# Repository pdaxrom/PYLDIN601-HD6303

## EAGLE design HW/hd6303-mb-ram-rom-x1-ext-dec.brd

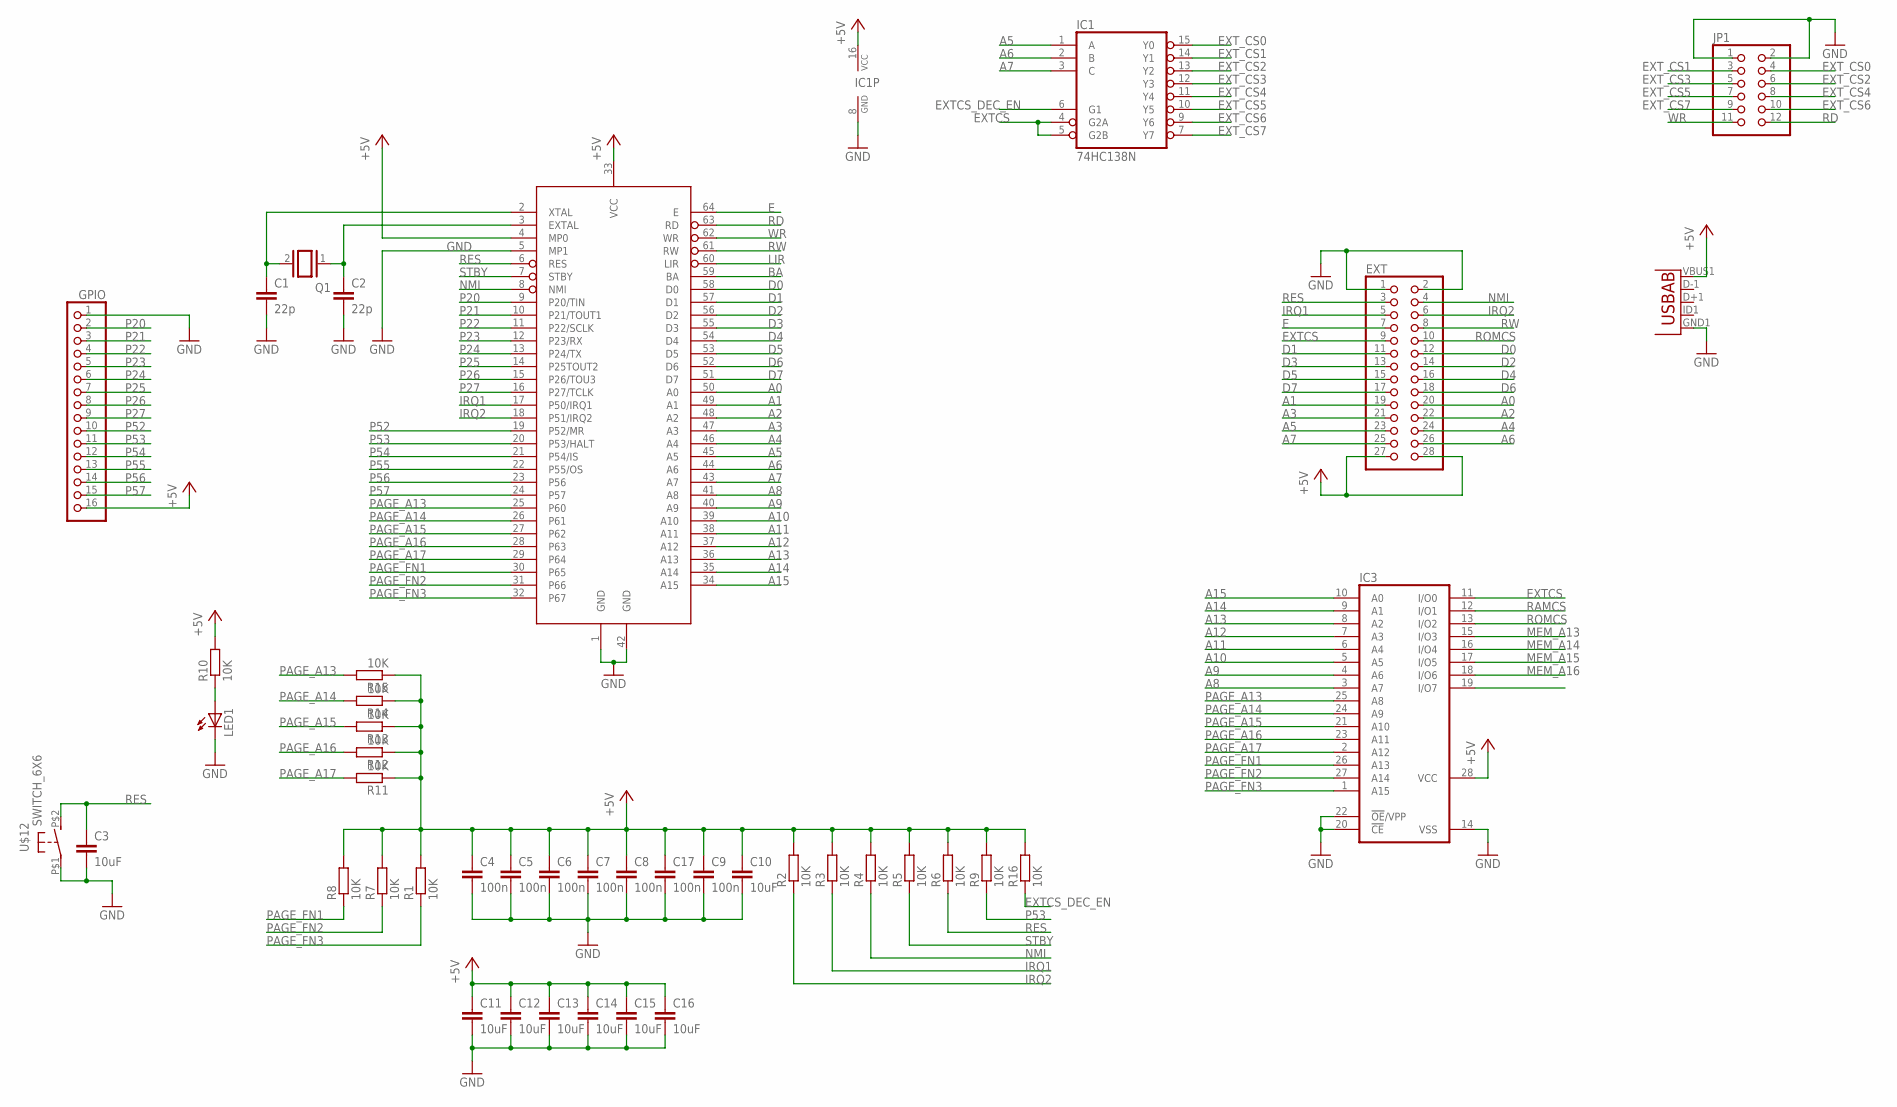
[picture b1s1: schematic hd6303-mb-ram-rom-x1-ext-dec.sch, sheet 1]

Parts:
C1, C2: 22p; C0603
C3, C10, C11, C12, C13, C14, C15, C16: 10uF; C0805
C4, C5, C6, C7, C8, C9, C17: 100n; C0603
EXT: PINHD-2X14; 2X14
GPIO: PINHD-1X16; 1X16
IC1: 74HC138N; DIL16
IC3: 27512G; DIL28-6
JP1: PINHD-2X6; 2X06
LED1: LED5MM
Q1: XTAL/S; QS
R1, R2, R3, R4, R5, R6, R7, R8, R9, R10, R11, R12, R13, R14, R15, R16: 10K; R0603
U2: USB""; USB-MICRO-SMD
U$1: HD6303YCP; DP-64S
U$12: SWITCH_6X6

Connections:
+5V: C4.1, C5.1, C6.1, C7.1, C8.1, C9.1, C10.1, C11.1, C12.1, C13.1, C14.1, C15.1, C16.1, C17.1, EXT.27, EXT.28, GPIO.16, IC1.16 (VCC), IC3.28 (VCC), R1.2, R2.2, R3.2, R4.2, R5.2, R6.2, R7.2, R8.2, R9.2, R10.2, R11.1, R12.1, R13.1, R14.1, R15.1, R16.2, U2.VBUS1 (VBUS), U$1.4 (MP0), U$1.33 (VCC); also elsewhere on the board
A0: EXT.20, U$1.50 (A0); also elsewhere on the board
A1: EXT.19, U$1.49 (A1); also elsewhere on the board
A2: EXT.22, U$1.48 (A2); also elsewhere on the board
A3: EXT.21, U$1.47 (A3); also elsewhere on the board
A4: EXT.24, U$1.46 (A4); also elsewhere on the board
A5: EXT.23, IC1.1 (A), U$1.45 (A5); also elsewhere on the board
A6: EXT.26, IC1.2 (B), U$1.44 (A6); also elsewhere on the board
A7: EXT.25, IC1.3 (C), U$1.43 (A7); also elsewhere on the board
A8: IC3.3 (A7), U$1.41 (A8); also elsewhere on the board
A9: IC3.4 (A6), U$1.40 (A9); also elsewhere on the board
A10: IC3.5 (A5), U$1.39 (A10); also elsewhere on the board
A11: IC3.6 (A4), U$1.38 (A11); also elsewhere on the board
A12: IC3.7 (A3), U$1.37 (A12); also elsewhere on the board
A13: IC3.8 (A2), U$1.36 (A13)
A14: IC3.9 (A1), U$1.35 (A14)
A15: IC3.10 (A0), U$1.34 (A15)
BA: U$1.59 (BA)
D0: EXT.12, U$1.58 (D0); also elsewhere on the board
D1: EXT.11, U$1.57 (D1); also elsewhere on the board
D2: EXT.14, U$1.56 (D2); also elsewhere on the board
D3: EXT.13, U$1.55 (D3); also elsewhere on the board
D4: EXT.16, U$1.54 (D4); also elsewhere on the board
D5: EXT.15, U$1.53 (D5); also elsewhere on the board
D6: EXT.18, U$1.52 (D6); also elsewhere on the board
D7: EXT.17, U$1.51 (D7); also elsewhere on the board
E: EXT.7, U$1.64 (E)
EXTCS: EXT.9, IC1.4 (G2A), IC1.5 (G2B), IC3.11 (I/O0)
EXTCS_DEC_EN: IC1.6 (G1), R16.1
EXT_CS0: IC1.15 (Y0), JP1.4
EXT_CS1: IC1.14 (Y1), JP1.3
EXT_CS2: IC1.13 (Y2), JP1.6
EXT_CS3: IC1.12 (Y3), JP1.5
EXT_CS4: IC1.11 (Y4), JP1.8
EXT_CS5: IC1.10 (Y5), JP1.7
EXT_CS6: IC1.9 (Y6), JP1.10
EXT_CS7: IC1.7 (Y7), JP1.9
GND: C1.2, C2.2, C3.2, C4.2, C5.2, C6.2, C7.2, C8.2, C9.2, C10.2, C11.2, C12.2, C13.2, C14.2, C15.2, C16.2, C17.2, EXT.1, EXT.2, GPIO.1, IC1.8 (GND), IC3.14 (VSS), IC3.20 (!CE), IC3.22 (!OE!/VPP), JP1.1, JP1.2, LED1.K (C), U2.GND1 (GND), U$1.1 (GND), U$1.5 (MP1), U$1.42 (GND), U$12.P$1; also elsewhere on the board
IRQ1: EXT.5, R3.1, U$1.17 (P50/IRQ1)
IRQ2: EXT.6, R2.1, U$1.18 (P51/IRQ2)
LIR: U$1.60 (LIR)
MEM_A13: IC3.15 (I/O3); also elsewhere on the board
MEM_A14: IC3.16 (I/O4); also elsewhere on the board
MEM_A15: IC3.17 (I/O5); also elsewhere on the board
MEM_A16: IC3.18 (I/O6); also elsewhere on the board
unnamed: LED1.A, R10.1
unnamed: C1.1, Q1.2, U$1.2 (XTAL)
unnamed: C2.1, Q1.1, U$1.3 (EXTAL)
NMI: EXT.4, R4.1, U$1.8 (NMI)
P20: GPIO.2, U$1.9 (P20/TIN)
P21: GPIO.3, U$1.10 (P21/TOUT1)
P22: GPIO.4, U$1.11 (P22/SCLK)
P23: GPIO.5, U$1.12 (P23/RX)
P24: GPIO.6, U$1.13 (P24/TX)
P25: GPIO.7, U$1.14 (P25TOUT2)
P26: GPIO.8, U$1.15 (P26/TOU3)
P27: GPIO.9, U$1.16 (P27/TCLK)
P52: GPIO.10, U$1.19 (P52/MR)
P53: GPIO.11, R9.1, U$1.20 (P53/HALT)
P54: GPIO.12, U$1.21 (P54/IS)
P55: GPIO.13, U$1.22 (P55/OS)
P56: GPIO.14, U$1.23 (P56)
P57: GPIO.15, U$1.24 (P57)
PAGE_A13: IC3.25 (A8), R15.2, U$1.25 (P60)
PAGE_A14: IC3.24 (A9), R14.2, U$1.26 (P61)
PAGE_A15: IC3.21 (A10), R13.2, U$1.27 (P62)
PAGE_A16: IC3.23 (A11), R12.2, U$1.28 (P63)
PAGE_A17: IC3.2 (A12), R11.2, U$1.29 (P64)
PAGE_FN1: IC3.26 (A13), R8.1, U$1.30 (P65)
PAGE_FN2: IC3.27 (A14), R7.1, U$1.31 (P66)
PAGE_FN3: IC3.1 (A15), R1.1, U$1.32 (P67)
RAMCS: IC3.12 (I/O1); also elsewhere on the board
RD: JP1.12, U$1.63 (RD); also elsewhere on the board
RES: C3.1, EXT.3, R6.1, U$1.6 (RES), U$12.P$2 (S)
ROMCS: EXT.10, IC3.13 (I/O2); also elsewhere on the board
RW: EXT.8, U$1.61 (RW)
STBY: R5.1, U$1.7 (STBY)
WR: JP1.11, U$1.62 (WR); also elsewhere on the board

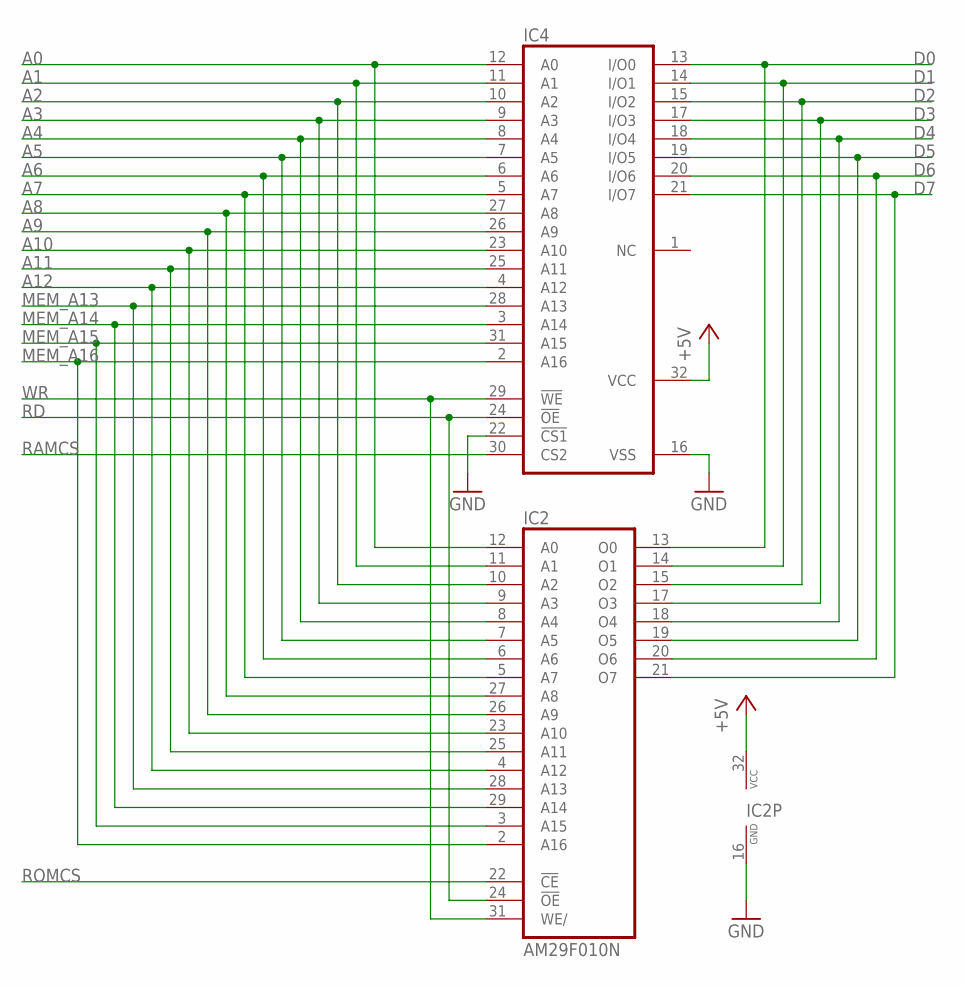
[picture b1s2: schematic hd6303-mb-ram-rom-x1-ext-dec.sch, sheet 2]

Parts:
IC2: AM29F010N; DIP32
IC4: 628128P; DIL32

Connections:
+5V: IC2.32 (VCC), IC4.32 (VCC); also elsewhere on the board
A0: IC2.12 (A0), IC4.12 (A0); also elsewhere on the board
A1: IC2.11 (A1), IC4.11 (A1); also elsewhere on the board
A2: IC2.10 (A2), IC4.10 (A2); also elsewhere on the board
A3: IC2.9 (A3), IC4.9 (A3); also elsewhere on the board
A4: IC2.8 (A4), IC4.8 (A4); also elsewhere on the board
A5: IC2.7 (A5), IC4.7 (A5); also elsewhere on the board
A6: IC2.6 (A6), IC4.6 (A6); also elsewhere on the board
A7: IC2.5 (A7), IC4.5 (A7); also elsewhere on the board
A8: IC2.27 (A8), IC4.27 (A8); also elsewhere on the board
A9: IC2.26 (A9), IC4.26 (A9); also elsewhere on the board
A10: IC2.23 (A10), IC4.23 (A10); also elsewhere on the board
A11: IC2.25 (A11), IC4.25 (A11); also elsewhere on the board
A12: IC2.4 (A12), IC4.4 (A12); also elsewhere on the board
D0: IC2.13 (O0), IC4.13 (I/O0); also elsewhere on the board
D1: IC2.14 (O1), IC4.14 (I/O1); also elsewhere on the board
D2: IC2.15 (O2), IC4.15 (I/O2); also elsewhere on the board
D3: IC2.17 (O3), IC4.17 (I/O3); also elsewhere on the board
D4: IC2.18 (O4), IC4.18 (I/O4); also elsewhere on the board
D5: IC2.19 (O5), IC4.19 (I/O5); also elsewhere on the board
D6: IC2.20 (O6), IC4.20 (I/O6); also elsewhere on the board
D7: IC2.21 (O7), IC4.21 (I/O7); also elsewhere on the board
GND: IC2.16 (GND), IC4.16 (VSS), IC4.22 (!CS1); also elsewhere on the board
MEM_A13: IC2.28 (A13), IC4.28 (A13); also elsewhere on the board
MEM_A14: IC2.29 (A14), IC4.3 (A14); also elsewhere on the board
MEM_A15: IC2.3 (A15), IC4.31 (A15); also elsewhere on the board
MEM_A16: IC2.2 (A16), IC4.2 (A16); also elsewhere on the board
RAMCS: IC4.30 (CS2); also elsewhere on the board
RD: IC2.24 (!OE), IC4.24 (!OE); also elsewhere on the board
ROMCS: IC2.22 (!CE); also elsewhere on the board
WR: IC2.31 (WE/), IC4.29 (!WE); also elsewhere on the board

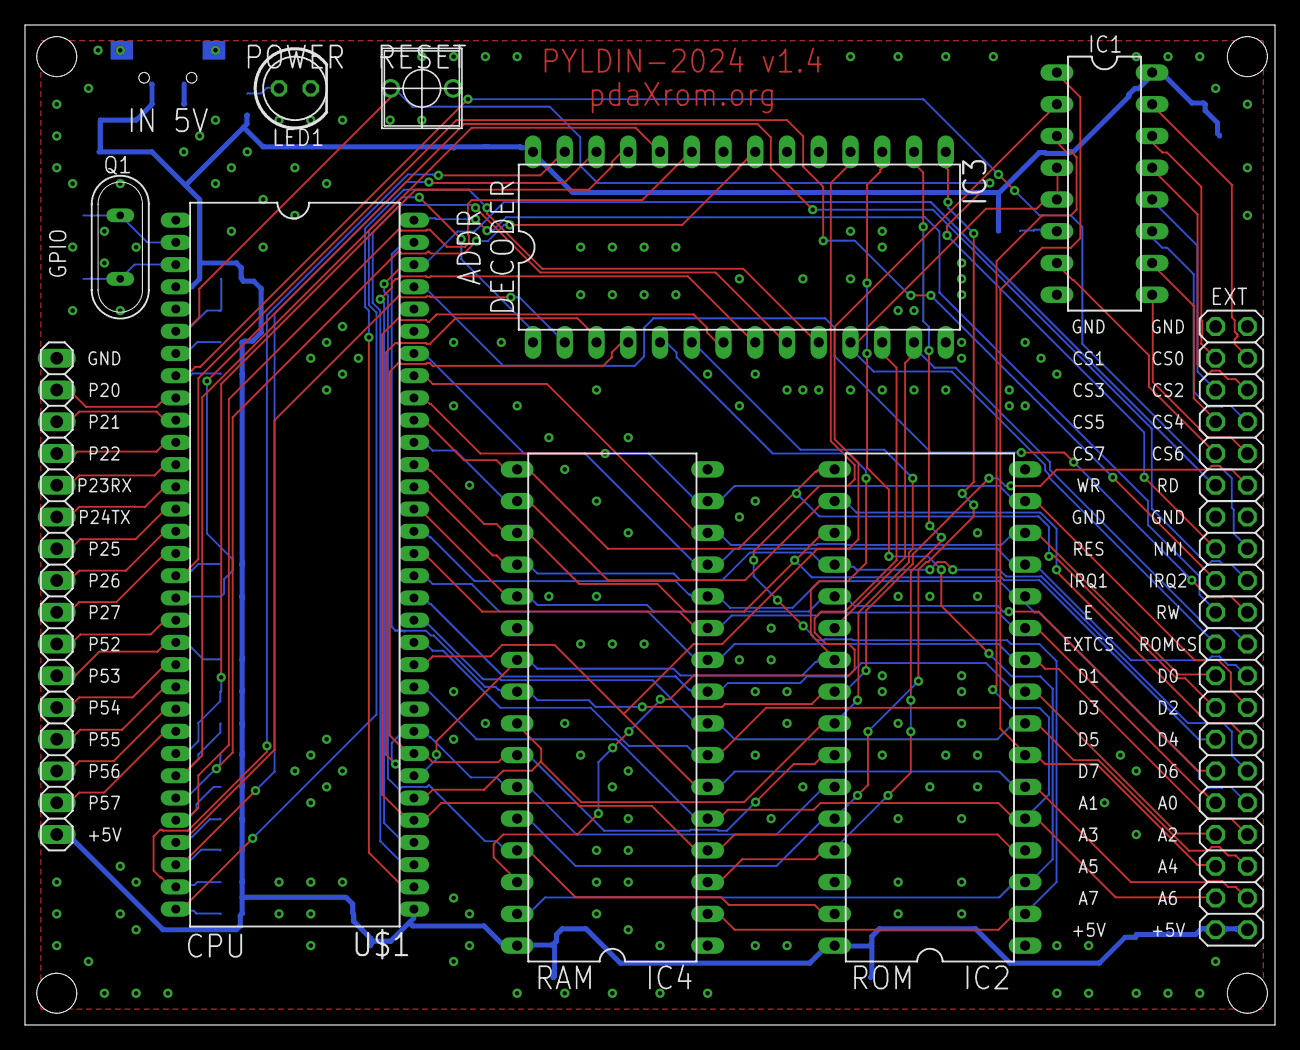
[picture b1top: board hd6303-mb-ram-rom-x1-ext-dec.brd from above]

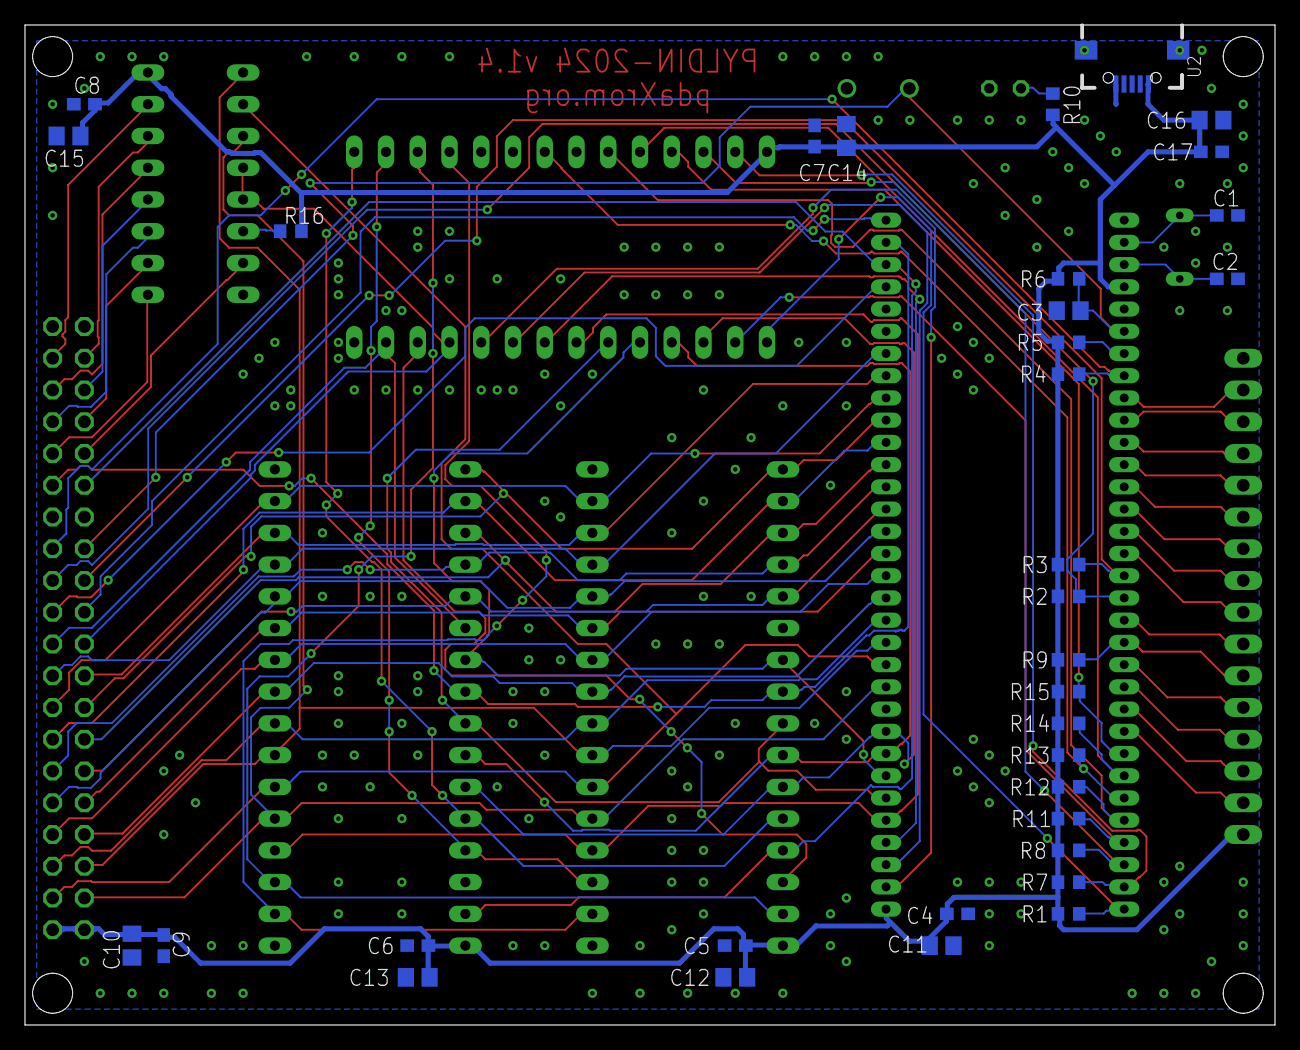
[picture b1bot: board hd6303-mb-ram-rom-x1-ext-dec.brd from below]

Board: 2 copper layers, 100.0 x 80.0 mm, 45 parts (34 on the bottom side), 76 nets.

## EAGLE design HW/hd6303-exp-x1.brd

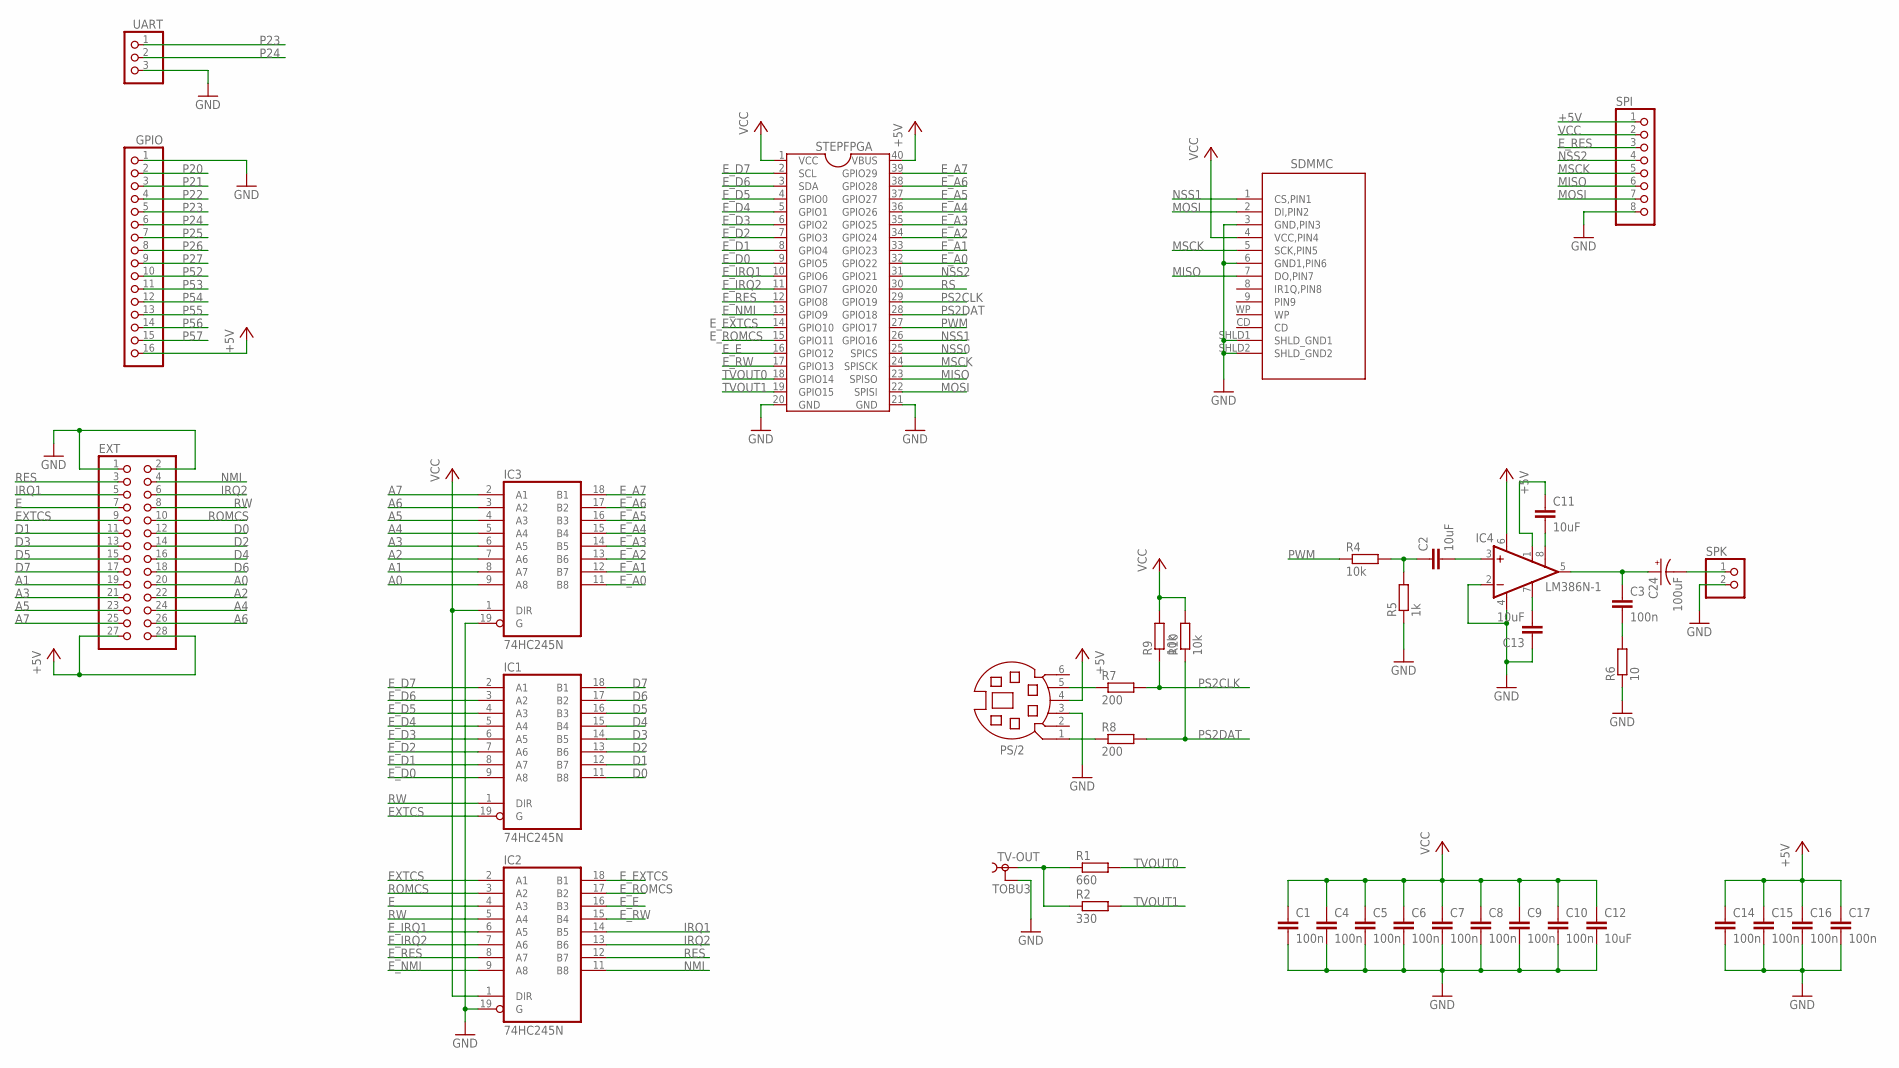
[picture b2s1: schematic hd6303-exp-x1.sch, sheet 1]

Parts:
C1, C3, C4, C5, C6, C7, C8, C9, C10, C14, C15, C16, C17: 100n; C0603
C2, C11, C12, C13: 10uF; C0805
C24: 100uF; EIA7343
EXT: PINHD-2X14; 2X14
GPIO: PINHD-1X16; 1X16
IC1, IC2, IC3: 74HC245N; DIL20
IC4: LM386N-1; DIL08
PS/2: MD06SS; MDIN06SS
R1: 660; R0603
R2: 330; R0603
R4, R9, R10: 10k; R0603
R5: 1k; R0603
R6: 10; R0603
R7, R8: 200; R0603
SDMMC: FCI_SD_SOCKET; SD-MMC_SOCKET-PP
SPI: PINHD-1X8; 1X08
SPK: PINHD-1X2; 1X02
STEPFPGA: STEPFPGA; DIL40
TV-OUT: TOBU3
UART: PINHD-1X3; 1X03

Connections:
+5V: C14.1, C15.1, C16.1, C17.1, EXT.27, EXT.28, GPIO.16, IC4.6 (VS), PS/2.4, SPI.1, STEPFPGA.40 (VBUS); also elsewhere on the board
A0: EXT.20, IC3.9 (A8)
A1: EXT.19, IC3.8 (A7)
A2: EXT.22, IC3.7 (A6)
A3: EXT.21, IC3.6 (A5)
A4: EXT.24, IC3.5 (A4)
A5: EXT.23, IC3.4 (A3)
A6: EXT.26, IC3.3 (A2)
A7: EXT.25, IC3.2 (A1)
D0: EXT.12, IC1.11 (B8)
D1: EXT.11, IC1.12 (B7)
D2: EXT.14, IC1.13 (B6)
D3: EXT.13, IC1.14 (B5)
D4: EXT.16, IC1.15 (B4)
D5: EXT.15, IC1.16 (B3)
D6: EXT.18, IC1.17 (B2)
D7: EXT.17, IC1.18 (B1)
E: EXT.7, IC2.4 (A3)
EXTCS: EXT.9, IC1.19 (G), IC2.2 (A1)
E_A0: IC3.11 (B8), STEPFPGA.32 (GPIO22)
E_A1: IC3.12 (B7), STEPFPGA.33 (GPIO23)
E_A2: IC3.13 (B6), STEPFPGA.34 (GPIO24)
E_A3: IC3.14 (B5), STEPFPGA.35 (GPIO25)
E_A4: IC3.15 (B4), STEPFPGA.36 (GPIO26)
E_A5: IC3.16 (B3), STEPFPGA.37 (GPIO27)
E_A6: IC3.17 (B2), STEPFPGA.38 (GPIO28)
E_A7: IC3.18 (B1), STEPFPGA.39 (GPIO29)
E_D0: IC1.9 (A8), STEPFPGA.9 (GPIO5)
E_D1: IC1.8 (A7), STEPFPGA.8 (GPIO4)
E_D2: IC1.7 (A6), STEPFPGA.7 (GPIO3)
E_D3: IC1.6 (A5), STEPFPGA.6 (GPIO2)
E_D4: IC1.5 (A4), STEPFPGA.5 (GPIO1)
E_D5: IC1.4 (A3), STEPFPGA.4 (GPIO0)
E_D6: IC1.3 (A2), STEPFPGA.3 (SDA)
E_D7: IC1.2 (A1), STEPFPGA.2 (SCL)
E_E: IC2.16 (B3), STEPFPGA.16 (GPIO12)
E_EXTCS: IC2.18 (B1), STEPFPGA.14 (GPIO10)
E_IRQ1: IC2.6 (A5), STEPFPGA.10 (GPIO6)
E_IRQ2: IC2.7 (A6), STEPFPGA.11 (GPIO7)
E_NMI: IC2.9 (A8), STEPFPGA.13 (GPIO9)
E_RES: IC2.8 (A7), SPI.3, STEPFPGA.12 (GPIO8); also elsewhere on the board
E_ROMCS: IC2.17 (B2), STEPFPGA.15 (GPIO11)
E_RW: IC2.15 (B4), STEPFPGA.17 (GPIO13)
GND: C1.2, C4.2, C5.2, C6.2, C7.2, C8.2, C9.2, C10.2, C12.2, C13.1, C14.2, C15.2, C16.2, C17.2, EXT.1, EXT.2, GPIO.1, IC1.10 (GND), IC2.10 (GND), IC2.19 (G), IC3.10 (GND), IC3.19 (G), IC4.2 (-IN), IC4.4 (GND), PS/2.3, R5.1, R6.1, SDMMC.3 (GND,PIN3), SDMMC.6 (GND1,PIN6), SDMMC.SHLD1 (SHLD_GND1), SDMMC.SHLD2 (SHLD_GND2), SPI.8, SPK.2, STEPFPGA.20 (GND), STEPFPGA.21 (GND), TV-OUT.2, TV-OUT.2@1 (2), TV-OUT.2@2 (2), UART.3; also elsewhere on the board
IRQ1: EXT.5, IC2.14 (B5)
IRQ2: EXT.6, IC2.13 (B6)
MISO: SDMMC.7 (DO,PIN7), SPI.6, STEPFPGA.23 (SPISO)
MOSI: SDMMC.2 (DI,PIN2), SPI.7, STEPFPGA.22 (SPISI); also elsewhere on the board
MSCK: SDMMC.5 (SCK,PIN5), SPI.5, STEPFPGA.24 (SPISCK); also elsewhere on the board
unnamed: C2.2, IC4.3 (+IN)
unnamed: C2.1, R4.2, R5.2
unnamed: R1.1, R2.1, TV-OUT.1
unnamed: C3.1, C24.A (+), IC4.5 (OUT)
unnamed: C3.2, R6.2
unnamed: C11.1, IC4.1 (GAIN)
unnamed: C11.2, IC4.8 (GAIN)
unnamed: C24.C (-), SPK.1
unnamed: C13.2, IC4.7 (BYPASS)
unnamed: PS/2.5, R7.1
unnamed: PS/2.1, R8.1
NMI: EXT.4, IC2.11 (B8)
NSS0: STEPFPGA.25 (SPICS); also elsewhere on the board
NSS1: SDMMC.1 (CS,PIN1), STEPFPGA.26 (GPIO16)
NSS2: SPI.4, STEPFPGA.31 (GPIO21)
P20: GPIO.2
P21: GPIO.3
P22: GPIO.4
P23: GPIO.5, UART.1
P24: GPIO.6, UART.2
P25: GPIO.7
P26: GPIO.8
P27: GPIO.9
P52: GPIO.10
P53: GPIO.11
P54: GPIO.12
P55: GPIO.13
P56: GPIO.14
P57: GPIO.15
PS2CLK: R7.2, R9.1, STEPFPGA.29 (GPIO19)
PS2DAT: R8.2, R10.1, STEPFPGA.28 (GPIO18)
PWM: R4.1, STEPFPGA.27 (GPIO17)
RES: EXT.3, IC2.12 (B7)
ROMCS: EXT.10, IC2.3 (A2)
RS: STEPFPGA.30 (GPIO20); also elsewhere on the board
RW: EXT.8, IC1.1 (DIR), IC2.5 (A4)
TVOUT0: R1.2, STEPFPGA.18 (GPIO14)
TVOUT1: R2.2, STEPFPGA.19 (GPIO15)
VCC: C1.1, C4.1, C5.1, C6.1, C7.1, C8.1, C9.1, C10.1, C12.1, IC1.20 (VCC), IC2.1 (DIR), IC2.20 (VCC), IC3.1 (DIR), IC3.20 (VCC), R9.2, R10.2, SDMMC.4 (VCC,PIN4), SPI.2, STEPFPGA.1 (VCC); also elsewhere on the board

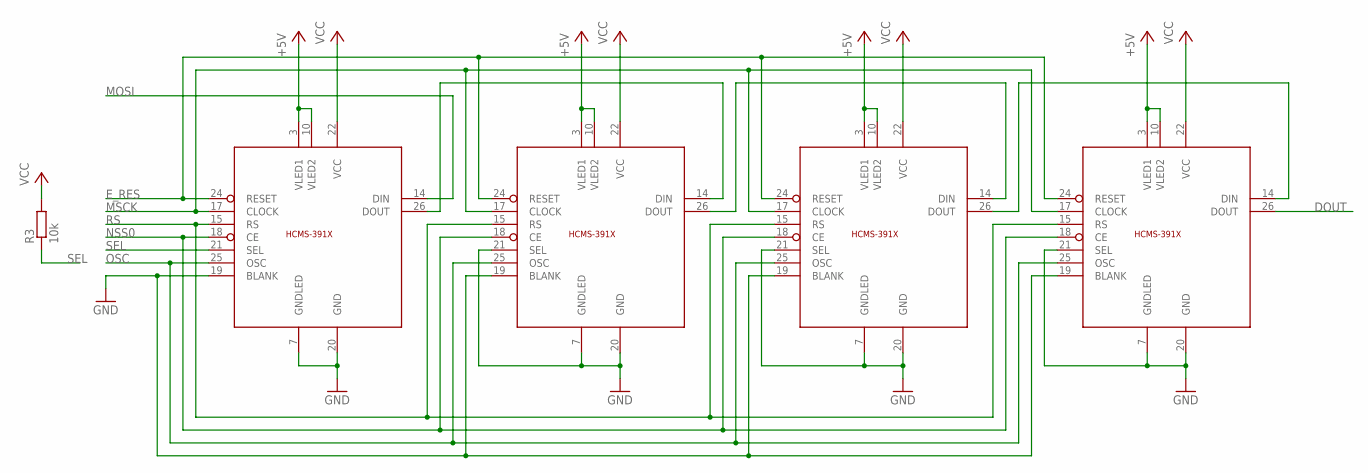
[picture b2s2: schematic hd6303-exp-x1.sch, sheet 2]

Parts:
R3: 10k; R0603
U$1, U$2, U$3, U$4: HCMS-391X

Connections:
+5V: U$1.3 (VLED1), U$1.10 (VLED2), U$2.3 (VLED1), U$2.10 (VLED2), U$3.3 (VLED1), U$3.10 (VLED2), U$4.3 (VLED1), U$4.10 (VLED2); also elsewhere on the board
DOUT: U$4.26 (DOUT)
E_RES: U$1.24 (RESET), U$2.24 (RESET), U$3.24 (RESET), U$4.24 (RESET); also elsewhere on the board
GND: U$1.7 (GNDLED), U$1.19 (BLANK), U$1.20 (GND), U$2.7 (GNDLED), U$2.19 (BLANK), U$2.20 (GND), U$2.21 (SEL), U$3.7 (GNDLED), U$3.19 (BLANK), U$3.20 (GND), U$3.21 (SEL), U$4.7 (GNDLED), U$4.19 (BLANK), U$4.20 (GND), U$4.21 (SEL); also elsewhere on the board
MOSI: U$1.14 (DIN); also elsewhere on the board
MSCK: U$1.17 (CLOCK), U$2.17 (CLOCK), U$3.17 (CLOCK), U$4.17 (CLOCK); also elsewhere on the board
unnamed: U$1.26 (DOUT), U$2.14 (DIN)
unnamed: U$2.26 (DOUT), U$3.14 (DIN)
unnamed: U$3.26 (DOUT), U$4.14 (DIN)
NSS0: U$1.18 (CE), U$2.18 (CE), U$3.18 (CE), U$4.18 (CE); also elsewhere on the board
OSC: U$1.25 (OSC), U$2.25 (OSC), U$3.25 (OSC), U$4.25 (OSC)
RS: U$1.15 (RS), U$2.15 (RS), U$3.15 (RS), U$4.15 (RS); also elsewhere on the board
SEL: R3.1, U$1.21 (SEL)
VCC: R3.2, U$1.22 (VCC), U$2.22 (VCC), U$3.22 (VCC), U$4.22 (VCC); also elsewhere on the board

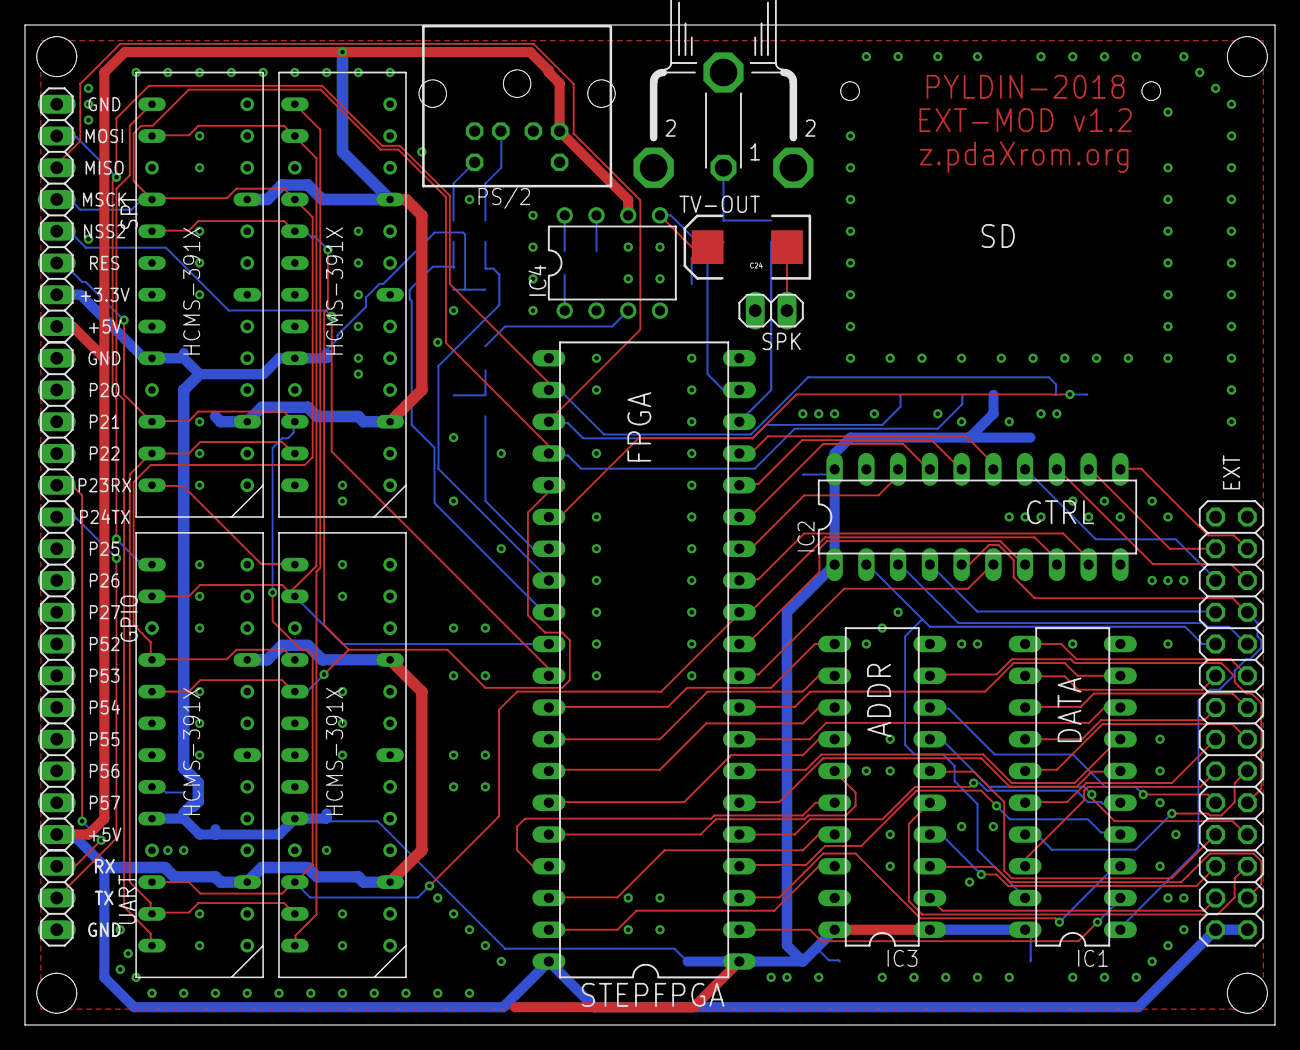
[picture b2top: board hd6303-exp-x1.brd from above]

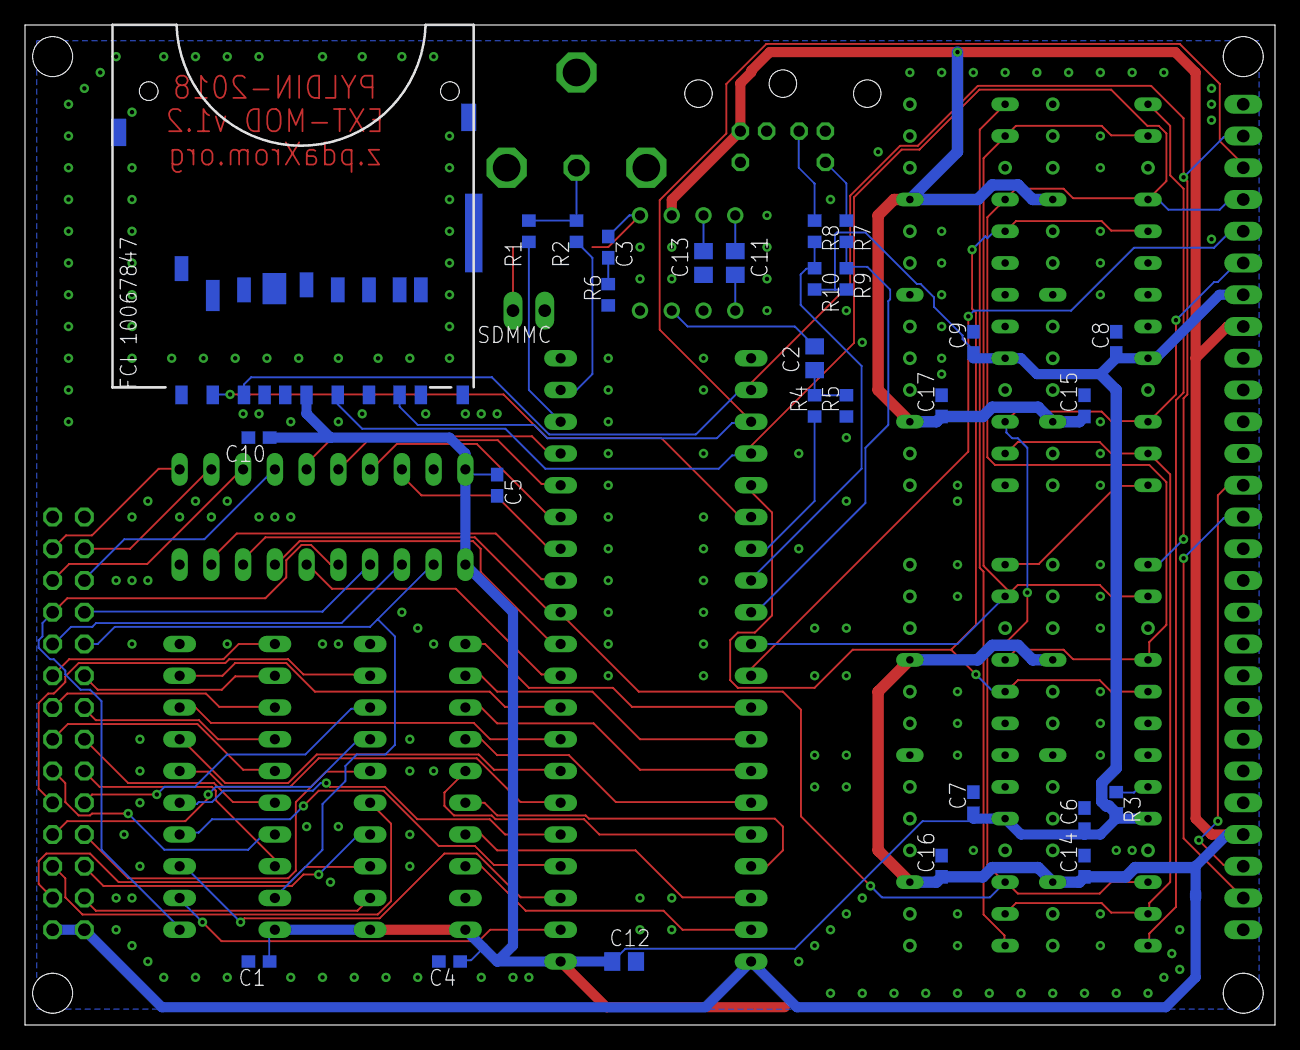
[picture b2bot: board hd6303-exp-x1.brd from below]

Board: 2 copper layers, 100.0 x 80.0 mm, 45 parts (28 on the bottom side), 81 nets.

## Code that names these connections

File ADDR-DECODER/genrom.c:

#include <stdio.h>

#define B(b) (b?1:0)

#define ROM_WIDTH	16

#define A15		(1 << 0)
#define A14		(1 << 1)
#define A13		(1 << 2)
#define A12		(1 << 3)
#define A11		(1 << 4)
#define A10		(1 << 5)
#define A9		(1 << 6)
#define A8		(1 << 7)
#define PAGE_A13	(1 << 8)
#define PAGE_A14	(1 << 9)
#define PAGE_A15	(1 << 10)
#define PAGE_A16	(1 << 11)
#define PAGE_A17	(1 << 12)
#define PAGE_FN1	(1 << 13)
#define PAGE_FN2	(1 << 14)
#define PAGE_FN3	(1 << 15)

#define EXTCS		(1 << 0)
#define RAMCS		(1 << 1)
#define ROMCS		(1 << 2)
#define MEM_A13		(1 << 3)
#define MEM_A14		(1 << 4)
#define MEM_A15		(1 << 5)
#define MEM_A16		(1 << 6)

int main(int argc, char *argv[])
{
    unsigned char rom[1 << ROM_WIDTH];
    unsigned int i;
    int oldout = 0;

    FILE *outf = fopen(argv[1], "wb");
    if (!outf) {
	fprintf(stderr, "Can't open output file!\n");
	return 1;
    }

    for (i = 0; i < sizeof(rom); i++) {
	unsigned char out = 0;

	/* PAGE 0xC000 0xD000 */
	if ((i & A15) && (i & A14) && !(i & A13)) {
	    if (i & PAGE_A17) {
		out |= EXTCS; // EXTCS = 1, RAMCS = 0, ROMCS = 0
		fprintf(stderr, "PROM> ");
	    } else {
		out |= (RAMCS | ROMCS | EXTCS); // EXTCS = 1, RAMCS = 1, ROMCS = 1
		fprintf(stderr, "PRAM> ");
	    }
	    out |= (((i & PAGE_A16) ? MEM_A16 : 0) |
		    ((i & PAGE_A15) ? MEM_A15 : 0) |
		    ((i & PAGE_A14) ? MEM_A14 : 0) |
		    ((i & PAGE_A13) ? MEM_A13 : 0));
	} else {
	    /* BIOS 0xF000 */
	    if ((i & A15) && (i & A14) && (i & A13) && (i & A12)) {
		out |= EXTCS; // EXTCS = 1, RAMCS = 0, ROMCS = 0
		fprintf(stderr, " ROM> ");
	    } else 
	    /* EXT 0xE600 */
	    if ((i & A15) && (i & A14) && (i & A13) && !(i & A12) &&
		!(i & A11) && (i & A10) && (i & A9) && !(i & A8)) {
		out |= ROMCS; // EXTCS = 0, RAMCS = 0, ROMCS = 1
		fprintf(stderr, " EXT> ");
	    } else {
		/* RAM */
		out |= (RAMCS | ROMCS | EXTCS); // EXTCS=1, RAMCS = 1, ROMCS = 1
		fprintf(stderr, " RAM> ");
	    }

	    out |= (((i & A15) ? MEM_A15 : 0) |
		    ((i & A14) ? MEM_A14 : 0) |
		    ((i & A13) ? MEM_A13 : 0));
	}

//	if (oldout != out) {
	    fprintf(stderr, "%d %d %d %d %d | %d %d %d %d %d %d %d %d X X X X X X X X - EXTCS=%d RAMCS=%d ROMCS=%d A16=%d A15=%d A14=%d A13=%d\n",
		B(i&PAGE_A17), B(i&PAGE_A16), B(i&PAGE_A15), B(i&PAGE_A14), B(i&PAGE_A13),
		B(i&A15), B(i&A14), B(i&A13), B(i&A12), B(i&A11), B(i&A10), B(i&A9), B(i&A8),
		B(out&EXTCS), B(out&RAMCS), B(out&ROMCS), B(out&MEM_A16), B(out&MEM_A15), B(out&MEM_A14), B(out&MEM_A13));
//	    oldout = out;
//	}
	rom[i] = out;
    }

    fwrite(rom, 1, sizeof(rom), outf);
    fclose(outf);
    return 0;
}

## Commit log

2018-12-23 initial
2018-12-25 pullup for page_a13-page_a17, fixed decoder rom
2018-12-25 superio initial
2018-12-25 io logic
2018-12-25 reset fixed
2018-12-25 fixed read/write for simpleio
2018-12-26 pyldin superio examples
2018-12-26 fixed irq
2018-12-26 HMCS display demo
2018-12-26 fixed missed nets
2018-12-26 spiio fix initial
2018-12-26 brightness
2018-12-28 tvout initial
2018-12-28 vpu grafics initial
2018-12-28 pll added
2018-12-29 vram, vrom, pll
2018-12-29 removed 16bit data, added HxV sizes
2018-12-29 text demo
2018-12-29 Text mode
2018-12-29 little optimization
2018-12-29 video irq
2018-12-29 video irq demo
2018-12-29 Cursor demo
2018-12-29 Cursor
2018-12-30 cursor horizontal position fix
2018-12-30 ym2149 initial
2018-12-30 PSG demo
2018-12-30 clear shift register to prevent wrong pixels in new line
2018-12-30 rampage check
2018-12-30 rompages
2018-12-30 flash detect
2019-01-01 bootrom moved to last page, p601 compatible page selector
2019-01-02 ps2 keyboard initial
2019-01-02 ps2 demo
2019-01-02 ps2 keyboard
2019-01-02 ps2 host-to-keyboard initial
2019-01-03 working ps2 keyboard (device2host, host2device)
2019-01-03 removed unused source
2019-01-03 PS2 demos
2019-01-15 bios loader
2019-01-15 Pyldin compatible BIOS initial
2019-01-16 minimal unibios demo
2019-01-16 text mode initial fixes
2019-01-16 clear screen fix
2019-01-16 some optimization
2019-01-16 scrolling
2019-01-16 ps2 irq demo
2019-01-16 separate includes for memory and devices
2019-01-16 shift, lock keys
2019-01-16 reset keyboard and leds
2019-01-17 normal keyboard table
2019-01-17 caps/cyr key codes
2019-01-17 shift table
2019-01-17 control table
2019-01-17 cyr tables
2019-01-17 full tables for capslock and shift
2019-01-17 decode shift/lock keys
2019-01-17 ps/2 keyboard irq handler
2019-01-17 working keyboard
2019-01-17 remove empty floppy int
2019-01-17 remove unimplemented printer int
2019-01-17 MMC io
2019-01-17 keyboard init timeout
2019-01-17 remove unnecessary check
2019-01-18 flashrom utility
2019-01-18 UniDOS kernel added
2019-01-18 int F9-FF - HD6303Y extra interrupts
2019-01-18 FLASH BIOS utility
2019-01-18 ask ram page to load
2019-01-18 fixed UniDOS kernel and serial bootloader
2019-01-18 sd/mmc driver
2019-01-18 UniDOS shell initial
2019-01-19 load page utility for unibios
2019-01-19 initial working port
2019-01-19 fixed wrong page on terminate int
2019-01-19 write enabled
2019-01-19 utils
2019-01-19 unibios data moved from zero page, broken music functions
2019-01-20 clear screen fixed
2019-01-20 move vpu to to prevent of write incorrect data from non native apps
2019-01-20 VPU moved to
2019-01-20 show time
2019-01-20 fix name
2019-01-21 show operation mode
2019-01-21 patched basic
2019-01-21 native cursor fix
2019-01-21 patcher
2019-01-22 optimization for HD6303
2019-01-22 reinit after r/w error
2019-01-23 offset and checksum
2019-01-25 xonix port initial
2019-01-26 Trap interrupt demo
2019-01-26 Fixed xonix game
2019-01-28 cyrillic keyboard layout, int 08 now pyldin-601m compatible
2019-01-28 renamed
2019-01-28 ctrl layout fix
2019-01-29 pause scan code added
2019-01-29 use release bit
2019-01-29 use hw bits for prefix codes E0, E1, F0
2019-01-29 hw bits for E0, E1, F0 codes
2019-01-30 uart chiptune
2019-01-30 led driver
2019-01-31 RAM CHECK
2019-01-31 Disabled AMRE, HLTE, MRE. Delay on PS/2 keyboard detect.
2019-01-31 CTRL+ALT+ALT+DEL - hardware reset
2019-01-31 led driver optimization
2019-02-03 small-c port from flex-os
2019-02-03 hd6303 optimization
2019-02-03 working small-c compiler
2019-02-08 smallc virtual machine
2019-02-09 function num args in primary arg, virtual machine complete functions, compiler for virtual machine without asm optimization
2019-02-09 6500 assembler
2019-02-09 native mc6801/hd6303 assembler
2019-02-10 command line args
2019-02-10 cmdline support
2019-02-10 pyldin compatible asm pseudoops
2019-02-10 evaluate expression
2019-02-11 fixed label names, new evaluator for math
2019-02-11 inverted byte for [pseudo]opcodes
2019-02-11 ignore cr symbol
2019-02-11 section pseudo-op
2019-02-11 export global symbols from procedures
2019-02-11 smallc and asm
2019-02-11 make standalone cross tools
2019-02-12 cross syntax fix
2019-02-12 error, list, trunc pseudo-ops
2019-02-12 show all lines in listing
2019-02-12 fixed listing file
2019-02-12 updated bootstrap asm
2019-02-12 error handling
2019-02-12 chksum, line counter
2019-02-12 better error handling
2019-02-12 checksum fixed, direct/extend mode checking
2019-02-12 address mode fixed
2019-02-12 bootstrap asm updated
2019-02-12 direct jsr fix, reverse index x fix
2019-02-12 nested procedures
2019-02-13 bit ops added
2019-02-13 fix usage info, added exit() function
2019-02-13 fixed strcmp, toupper, tolower functions
2019-02-13 use streq instead of strcmp
2019-02-13 UniBIOS font
2019-02-13 as03 as primary compiler
2019-02-13 as03 as assembler
2019-02-18 file r/w functions, pgm output for assembler
2019-02-19 removed self modified code
2019-02-19 system, errno, errstr functions
2019-02-19 fixed names
2019-02-19 check for unopened fd
2019-02-19 Virtual Machine moved to ROM
2019-02-28 char driver for hcms display
2019-03-07 make boot utility - create bootsector
2019-03-07 sd format utility (15MB)
2019-03-08 show ram/rom pages info
2019-03-08 zcode moved to secondary rom space
2019-03-09 correct spi timing
2019-03-09 fixed wron address mode for PGM files
2019-03-10 irq router
2019-03-10 peripheral interrupts router
2019-03-10 interrupt router sample
2019-03-10 initial p601 graphics emulator
2019-03-11 removed obsolete sources
2019-03-11 removed low level samples for mcu rom
2019-03-11 FLASHBIOS utility
2019-03-11 ram test
2019-03-11 fixed sources directories
2019-03-11 common makefile
2019-03-11 Set theme jekyll-theme-hacker
2019-03-11 cpu-mem board photo
2019-03-11 moved pages
2019-03-11 Create CNAME
2019-03-11 Update CNAME
2019-03-11 Update README.md
    mainboard information
2019-03-11 ext-mod photo
2019-03-11 fixed name
2019-03-12 fixed screen bitblit
2019-03-14 condition directives
2019-03-15 6800 v2.52
2019-03-15 more compatibility with cross/6800
2019-03-15 define cmd parameter
2019-03-15 updated to latest version
2019-03-15 use BIOS functions to screen output to prevent to call page code
2019-03-15 YGP interpretator original
2019-03-15 UE original
2019-03-15 nested include files
2019-03-15 Makefile
2019-03-16 fixed computer name address
2019-03-16 hw configuration switch
2019-03-16 pgm fime
2019-03-16 fixed wrong mempage setup
2019-03-16 breakpoint call INT
2019-03-16 enabled pascal for lilith hardware
2019-03-16 fixed UE for lilith hardware
2019-03-17 virtual machine wrapper for native utils
2019-03-17 uasm source
2019-03-17 more ints - ulink support
2019-03-17 pages for web
2019-03-18 hw image
2019-03-19 10 fps
2019-03-21 fixed int 7 - dont change locked page, added quit from serial bootloader
2019-03-21 updated to 3.12
2019-03-21 dos utils
2019-03-28 motherboard v1.3
2019-05-04 released in pcb
2020-08-18 Fixed for GCC9 - strcpy replaced with memmove
2020-11-24 fix diamond path
2024-10-13 traced pcb
2024-10-14 fixes
2024-10-15 current version
